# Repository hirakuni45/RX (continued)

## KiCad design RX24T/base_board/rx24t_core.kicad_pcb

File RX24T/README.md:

## RX24T features / 特徴

- RXv2 core / RXv2 コア
- Maximum operating frequency 80MHz / 最大動作周波数 80MHz
- Single-precision 32-bit floating point / 32 ビット単精度浮動小数点
- 2.7V ～ 5.5V Operation / 動作
- 12 Bits A/D / １２ビットＡ／Ｄ変換器
- 8 Bits D/A / ８ビットＤ／Ａ変換器

### Package/パッケージ

|R5F524T---XX|Package/パッケージ|Pin/ピン数|Pitch/ピッチ|
|---|:-:|:-:|:-:|
|R5F524TxxxFP|LFQFP|100|0.50|
|R5F524TxxxFF|LQFP|80|0.65|
|R5F524TxxxFN|LFQFP|80|0.50|
|R5F524TxxxFM|LFQFP|64|0.50|

### Ambient operating temperature/動作周囲温度

|R5F524T--X--|degree Celsius|
|---|:-:|
|R5F524TxxDxx|-40 ～ +85℃|

### Memoey size/メモリ容量

|R5F524TX----|CodeFlash|RAM|DataFlash|ChipVersion|
|---|:-:|:-:|:-:|:-:|
|R5F524TExxxx|512K|32K|8K|B|
|R5F524TCxxxx|384K|32K|8K|B|
|R5F524TBxxxx|256K|32K|8K|B|
|R5F524TAxxxx|256K|16K|8K|A|
|R5F524T8xxxx|128K|16K|8K|A|

### Data Flash/データ・フラッシュ

|Capacity|Erase Size|Blank Check Size|Write Size|Erase Value|ID|
|:-:|:-:|:-:|:-:|:-:|:-:|
|8K|1024|1/1024|1|0xFF|4|

---

## RX24T Linker file / リンカーファイル

|Type|Code Flash|RAM|Data Flash|Linker File|Ustack|Istack|
|---|:-:|:-:|:-:|---|:-:|:-:|
|R5F524TA|256K|16K|8K|[R5F524TA.ld](R5F524TA.ld?ts=4)|1024|512|
|R5F524T8|128K|16K|8K|[R5F524T8.ld](R5F524T8.ld?ts=4)|1024|512|

---

## RX24T Dedicated class / 専用クラス

|Function/機能|Source|Remarks/備考|
|---|---|:-:|
|Peripheral Name/ペリフェラル名|[peripheral.hpp](peripheral.hpp?ts=4)||
|Hardware-specific Definition/ハード固有定義|[board_profile.hpp](board_profile.hpp?ts=4)||
|Operating Frequency Definition/動作周波数定義|[clock_profile.hpp](clock_profile.hpp?ts=4)||
|Power Control/電力制御|[power_mgr.hpp](power_mgr.hpp?ts=4)||
|Port Definition/ポート定義|[port.hpp](port.hpp?ts=4)||
|Interrupt Definition/割り込み定義|[icu.hpp](icu.hpp?ts=4)||
|Interrupt Management/割り込み管理|[icu_mgr.hpp](icu_mgr.hpp?ts=4)||
|Port Function Definition/ポート機能定義|[mpc.hpp](mpc.hpp?ts=4)||
|Port Mapping/ポートマッピング|[port_map.hpp](port_map.hpp?ts=4)||
|Port Mapping IRQ/ポートマッピング IRQ|[port_map_irq.hpp](port_map_irq.hpp?ts=4)||
|Port Mapping MTU/ポートマッピング MTU|[port_map_mtu.hpp](port_map_mtu.hpp?ts=4)||
|Port Mapping TMR/ポートマッピング TMR|[port_map_tmr.hpp](port_map_tmr.hpp?ts=4)||
|Port Mapping GPT/ポートマッピング GPT|[port_map_gpt.hpp](port_map_gpt.hpp?ts=4)||
|FLASH Definition/FLASH 定義|[flash.hpp](flash.hpp?ts=4)||
|FLASH Definition/FLASH I/O 定義|[flash_io.hpp](flash_io.hpp?ts=4)||
|LVDA Definition/LVDA 定義|[lvda.hpp](lvda.hpp?ts=4)||
|POE3 Definition/POE3 定義|[poe2.hpp](poe3.hpp?ts=4)||
|D/A Definition/D/A 定義|[da.hpp](da.hpp?ts=4)||
|A/D Definition/A/D 定義|[s12ad.hpp](s12ad.hpp?ts=4)||
|System Definition/システム定義|[system.hpp](system.hpp?ts=4)||
|System I/O Definition/システム I/O 定義|[system_io.hpp](system_io.hpp?ts=4)||

---

## Basic Pin Assignments / 基本ピンアサイン

|Terminal/端子|LFQFP 100|
|---|---|
|VCL|VCL(5)|
|Reset Input/リセット入力|RES#(10)|
|Mode Controle/モード制御|MD/FINED(6)|
|RXD|PD5/RXD1(20)|
|TXD|PD3/TXD1(22)|
|Power/電源|VCC(14), VCC(29), VCC(42), VCC(60)|
|GND/接地|VSS(3), VSS(12), VSS(31), VSS(44), VSS(62)|
|Analog Power/アナログ電源|AVCC0(93), AVCC1(92), AVCC2(71)|
|Analog GND/アナログ接地|AVSS0(94), AVSS1(95), AVSS2(73)|
|Analog Refarence/アナログ基準電源|VREF(72)|
|OSC in|EXTAL(13)|
|OSC out|XTAL(11)|

- VCL: 4.7uF/25V

|Mode/モード|MD|
|---|:---:|
|Serial BOOT/シリアルブート|0|
|Single Chip/シングルチップ|1|

---

## Device, Renesas / デバイス、ルネサス

- [device.hpp (SIG_RX24T)](../common/device.hpp?ts=4)
- [renesas.hpp (SIG_RX24T)](../common/renesas.hpp?ts=4)

|name space|Device, Renesas|デバイス、ルネサス|
|---|---|---|
|[clock_profile](../RX24T/clock_profile?ts=4)|Clock Profile|クロック・プロファイル|
|[SYSTEM](../RX24T/system.hpp?ts=4)|Clock Generation Circuit|クロック発生回路|
|[power_mgr](../RX24T/power_mgr.hpp?ts=4)|Low Power Consumption|消費電力低減機能|
|[ICU](../RX24T/icu.hpp?ts=4)|Interrupt Controller|割り込みコントローラ|
|[icu_mgr](../RX24T/icu_mgr.hpp?ts=4)|ICU Manager|ICU マネージャー|
|[MPC](../RX24T/mpc.hpp?ts=4)|Multi-Function Pin Controller|マルチファンクションピンコントローラ|
|[PORTx](../RX24T/port.hpp?ts=4)|I/O Ports|I/O ポート|
|[port_map](../RX24T/port_map.hpp?ts=4)|Port Mapping|ポート・マッピング|
|[port_map_mtu](../RX24T/port_map_mtu.hpp?ts=4)|Port Mapping MTU|ポート・マッピング MTU|
|[port_map_tmr](../RX24T/port_map_tmr.hpp?ts=4)|Port Mapping TMR|ポート・マッピング TMR|
|[port_map_irq](../RX24T/port_map_irq.hpp?ts=4)|Port Mapping IRQ|ポート・マッピング IRQ|
|[FLASH](../RX24T/flash.hpp?ts=4)|Flash Memory|フラッシュメモリ|
|[SYSTEM_IO](../RX24T/system_io.hpp?ts=4)|System In/Out (Clock Setting)|システム In/Out (クロック設定)|
|[FLASH_IO](../RX24T/flash_io.hpp?ts=4)|Flash In/Out|フラッシュ In/Out|
|[adc_in](../RX24T/adc_in.hpp?ts=4)|A/D Converter Input|A/D 変換入力|
|[dac_out](../RX24T/dac_out.hpp?ts=4)|D/A Converter Output|D/A 変換出力|
|[board_profile](../RX24T/board_profile?ts=4)|Board Profile|ボード・プロファイル|

---

## Peripheral / ペリフェラル

- [peripheral.hpp](peripheral.hpp?ts=4)

|Peripheral|Function|機能|
|---|---|---|
|[CAC](../RX600/cac.hpp?ts=4)|Clock Frequency Accuracy Measurement Circuit|クロック周波数精度測定回路|
|[DTC](../RX600/dtc.hpp?ts=4)|Data Transfer Controller|データトランスファコントローラ|
|[MTU0](../RX600/mtu3.hpp?ts=4)|Multi-Function Timer Pulse Unit 0|マルチファンクションタイマパルスユニット０|
|[MTU1](../RX600/mtu3.hpp?ts=4)|Multi-Function Timer Pulse Unit 1|マルチファンクションタイマパルスユニット１|
|[MTU2](../RX600/mtu3.hpp?ts=4)|Multi-Function Timer Pulse Unit 2|マルチファンクションタイマパルスユニット２|
|[MTU3](../RX600/mtu3.hpp?ts=4)|Multi-Function Timer Pulse Unit 3|マルチファンクションタイマパルスユニット３|
|[MTU4](../RX600/mtu3.hpp?ts=4)|Multi-Function Timer Pulse Unit 4|マルチファンクションタイマパルスユニット４|
|[MTU5](../RX600/mtu3.hpp?ts=4)|Multi-Function Timer Pulse Unit 5|マルチファンクションタイマパルスユニット５|
|[MTU6](../RX600/mtu3.hpp?ts=4)|Multi-Function Timer Pulse Unit 6|マルチファンクションタイマパルスユニット６|
|[MTU7](../RX600/mtu3.hpp?ts=4)|Multi-Function Timer Pulse Unit 7|マルチファンクションタイマパルスユニット７|
|[MTU9](../RX600/mtu3.hpp?ts=4)|Multi-Function Timer Pulse Unit 9|マルチファンクションタイマパルスユニット９|
|[POE3](../RX600/poe3.hpp?ts=4)|Port Output Enable 3|ポートアウトプットイネーブル３|
|[GPT0](../RX600/gpt.hpp?ts=4)|General PWM Timer 0|汎用 PWM タイマ０|
|[GPT1](../RX600/gpt.hpp?ts=4)|General PWM Timer 1|汎用 PWM タイマ１|
|[GPT2](../RX600/gpt.hpp?ts=4)|General PWM Timer 2|汎用 PWM タイマ２|
|[GPT3](../RX600/gpt.hpp?ts=4)|General PWM Timer 3|汎用 PWM タイマ３|
|[TMR0](../RX600/tmr.hpp?ts=4)|8-Bit Timer 0|8 ビットタイマ０|
|[TMR1](../RX600/tmr.hpp?ts=4)|8-Bit Timer 1|8 ビットタイマ１|
|[TMR2](../RX600/tmr.hpp?ts=4)|8-Bit Timer 2|8 ビットタイマ２|
|[TMR3](../RX600/tmr.hpp?ts=4)|8-Bit Timer 3|8 ビットタイマ３|
|[TMR4](../RX600/tmr.hpp?ts=4)|8-Bit Timer 4|8 ビットタイマ４|
|[TMR5](../RX600/tmr.hpp?ts=4)|8-Bit Timer 5|8 ビットタイマ５|
|[TMR6](../RX600/tmr.hpp?ts=4)|8-Bit Timer 6|8 ビットタイマ６|
|[TMR7](../RX600/tmr.hpp?ts=4)|8-Bit Timer 7|8 ビットタイマ７|
|[CMT0](../RX600/cmpc.hpp?ts=4)|Compare Match Timer 0|コンペアマッチタイマ０|
|[CMT1](../RX600/cmpc.hpp?ts=4)|Compare Match Timer 1|コンペアマッチタイマ１|
|[CMT2](../RX600/cmpc.hpp?ts=4)|Compare Match Timer 2|コンペアマッチタイマ２|
|[CMT3](../RX600/cmpc.hpp?ts=4)|Compare Match Timer 3|コンペアマッチタイマ３|
|[IWDT](../RX600/iwdt.hpp?ts=4)|Independent Watchdog Timer|独立ウォッチドッグタイマ|
|[SCI1](../RX600/sci_g.hpp?ts=4)|Serial Communications Interface 1|シリアルコミュニケーションインタフェース１|
|[SCI5](../RX600/sci_g.hpp?ts=4)|Serial Communications Interface 5|シリアルコミュニケーションインタフェース５|
|[SCI6](../RX600/sci_g.hpp?ts=4)|Serial Communications Interface 6|シリアルコミュニケーションインタフェース６|
|[RIIC0](../RX600/riic.hpp?ts=4)|I2C-bus Interface 0|I2C バスインタフェース０|
|[RSCAN](../RX600/rscan.hpp?ts=4)|RSCAN Module|RSCAN モジュール|
|[RSPI0](../RX600/rspi.hpp?ts=4)|Serial Peripheral Interface 0|シリアルペリフェラルインタフェース０|
|[CRC](../RX600/crc.hpp?ts=4)|CRC Calculator|CRC 演算器|
|[S12AD](../RX24T/s12ad.hpp?ts=4)|12-Bit A/D Converter|12 ビット A/D コンバータ|
|[S12AD1](../RX24T/s12ad.hpp?ts=4)|12-Bit A/D Converter 1|12 ビット A/D コンバータ１|
|[S12AD2](../RX24T/s12ad.hpp?ts=4)|12-Bit A/D Converter 2|12 ビット A/D コンバータ２|
|[DA](../RX24T/da.hpp?ts=4)|8-Bit D/A Converter|8 ビット D/A コンバータ|
|[CMPC0](../RX600/cmpc.hpp?ts=4)|Comparator C0|コンパレーターＣ０|
|[CMPC1](../RX600/cmpc.hpp?ts=4)|Comparator C1|コンパレーターＣ１|
|[CMPC2](../RX600/cmpc.hpp?ts=4)|Comparator C2|コンパレーターＣ２|
|[CMPC3](../RX600/cmpc.hpp?ts=4)|Comparator C3|コンパレーターＣ３|
|[DOC](../RX600/doc.hpp?ts=4)|Data Operation Circuit|データ演算回路|

---

## Port map order (IRQ) / ポートマップ候補 (IRQ)

- [port_map_irq.hpp](port_map_irq.hpp?ts=4)

### LFQGFP100

|IRQ|FIRST|SECOND|THIRD|FOURTH|FIFTH|
|---|---|---|---|---|---|
|IRQ0|P10 (100)|P52 (81)|PE5 (1)|-|-|
|IRQ1|P11 (99)|P53 (80)|PA5 (36)|PE4 (8)|-|
|IRQ2|P00 (4)|P54 (79)|PD4 (21)|PE3 (9)|-|
|IRQ3|P55 (78)|PB4 (30)|PD5 (20)|-|-|
|IRQ4|P01 (7)|P60 (77)|P96 (43)|-|-|
|IRQ5|P02 (2)|P61 (76)|P70 (57)|PB6 (27)|PD6 (19)|
|IRQ6|P21 (67)|P31 (61)|P62 (75)|-|-|
|IRQ7|P20 (68)|P30 (63)|P63 (74)|-|-|

---

## Port map order / ポートマップ候補

- [port_map.hpp](port_map.hpp?ts=4)

### LFQFP100

|Peripheral|FIRST|SECOND|THIRD|
|---|---|---|---|
|SCI1 / RXD|PD5 (20)|-|-|
|SCI1 / TXD|PD3 (22)|-|-|
|SCI1 / SCK|PD4 (21)|-|-|
|SCI5 / RXD|PB6 (27)|PE0 (17)|-|
|SCI5 / TXD|PB5 (28)|PD7 (18)|-|
|SCI5 / SCK|PB7 (26)|PD2 (23)|-|
|SCI6 / RXD|P80 (98)|PA5 (36)|PB1 (34)|
|SCI6 / TXD|P81 (97)|PB0 (35)|PB2 (33)|
|SCI6 / SCK|P82 (96)|PA4 (37)|PB3 (32)|
|RIIC0 / SCL|PB1 (34)|-|-|
|RIIC0 / SDA|PB2 (33)|-|-|
|RSCAN / CRX|PA0 (41)|-|-|
|RSCAN / CTX|PA1 (40)|-|-|
|RSPI0 / RSPCK|P24 (64)|PB3 (32)|PD0 (25)|
|RSPI0 / MOSI|P23 (65)|PB0 (35)|PD2 (23)|
|RSPI0 / MISO|P22 (66)|PA5 (36)|PD1 (24)|
|RSPI0 / SSL0|P30 (63)|PA3 (38)|PD6 (19)|
|RSPI0 / SSL1|P31 (61)|PA2 (39)|PD7 (18)|
|RSPI0 / SSL2|P32 (59)|PA1 (40)|PE0 (17)|
|RSPI0 / SSL3|P33 (58)|PA0 (41)|PE1 (16)|

---

## Port map order (GPT) / ポートマップ候補 (GPT)

- [port_map_gpt.hpp](port_map_gpt.hpp?ts=4)

### LFQFP100

|GPT|FIRST|SECOND|THIRD|
|---|---|---|---|
|GTIOC0A|P71 (56)|PD7 (18)|-|
|GTIOC0B|P74 (53)|PD1 (24)|-|
|GTIOC1A|P72 (55)|PD0 (25)|-|
|GTIOC1B|P75 (52)|PB7 (26)|-|
|GTIOC2A|P73 (54)|PB6 (27)|-|
|GTIOC2B|P76 (51)|PB5 (28)|-|
|GTIOC3A|PD7 (18)|-|-|
|GTIOC3B|PD6 (19)|-|-|
|GTECLKA|PD5 (20)|-|-|
|GTECLKB|PD4 (21)|-|-|
|GTECLKC|PD3 (22)|-|-|
|GTECLKD|PB4 (30)|-|-|
|GTETRG|PB4 (30)|-|-|
|GTADSM0|PA3 (38)|-|-|
|GTADSM1|PA2 (39)|-|-|

---

## Port map order (MTU) / ポートマップ候補 (MTU)

[port_map_mtu.hpp](port_map_mtu.hpp?ts=4)

### LFQGFP100

|MTU|FIRST|SECOND|THIRD|
|---|---|---|---|
|MTIOC0A #|P31 (61)|PB3 (32)|-|
|MTIOC0B #|P30 (63)|PB2 (33)|-|
|MTIOC0C #|PB1 (34)|-|-|
|MTIOC0D #|PB0 (35)|-|-|
|MTIOC1A #|PA5 (36)|-|-|
|MTIOC1B #|PA4 (37)|-|-|
|MTIOC2A #|PA3 (38)|-|-|
|MTIOC2B #|PA2 (39)|-|-|
|MTIOC3A #|P11 (99)|P33 (58)|-|
|MTIOC3B #|P71 (56)|-|-|
|MTIOC3C #|P32 (59)|-|-|
|MTIOC3D #|P74 (53)|-|-|
|MTIOC4A #|P72 (55)|-|-|
|MTIOC4B #|P73 (54)|-|-|
|MTIOC4C #|P75 (52)|-|-|
|MTIOC4D #|P76 (51)|-|-|
|MTIC5U #|P24 (64)|P82 (96)|-|
|MTIC5V #|P23 (65)|P81 (97)|-|
|MTIC5W #|P22 (66)|P80 (98)|-|
|MTIOC6A #|PA1 (40)|-|-|
|MTIOC6B #|P95 (45)|-|-|
|MTIOC6C #|PA0 (41)|-|-|
|MTIOC6D #|P92 (48)|-|-|
|MTIOC7A #|P94 (46)|-|-|
|MTIOC7B #|P93 (47)|-|-|
|MTIOC7C #|P91 (49)|-|-|
|MTIOC7D #|P90 (50)|-|-|
|MTIOC9A #|P21 (67)|PD7 (18)|-|
|MTIOC9B #|P10 (100)|PE0 (17)|-|
|MTIOC9C #|P20 (68)|PD6 (19)|-|
|MTIOC9D #|P02 (2)|PE1 (16)|-|
|MTCLKA #|P21 (67)|P33 (58)|-|
|MTCLKB #|P20 (68)|P32 (59)|-|
|MTCLKC #|P11 (99)|P31 (61)|PE4 (8)|
|MTCLKD #|P10 (100)|P30 (63)|PE3 (9)|
|ADSM0|PB2 (33)|-|-|
|ADSM1|PB1 (34)|-|-|

---

## Port map order (TMR) / ポートマップ候補 (TMR)

- [port_map_tmr.hpp](port_map_tmr.hpp?ts=4)

### LFQFP100

|TMR|FIRST|SECOND|THIRD|FOURTH|
|---|---|---|---|---|
|TMO0|PD3 (22)|P33 (58)|PB0 (35)|-|
|TMCI0|PD4 (21)|PB1 (34)|-|-|
|TMRI0|PD5 (20)|PB2 (33)|-|-|
|TMO1|PD6 (19)|-|-|-|
|TMCI1|PD2 (23)|PE0 (17)|-|-|
|TMRI1|PD7 (18)|-|-|-|
|TMO2|P23 (65)|PA0 (41)|PD1 (24)|-|
|TMCI2|P24 (64)|-|-|-|
|TMRI2|P22 (66)|-|-|-|
|TMO3|P11 (99)|-|-|-|
|TMCI3|PA5 (36)|-|-|-|
|TMRI3|P10 (100)|-|-|-|
|TMO4|P22 (66)|P82 (96)|PA1 (40)|PD2 (23)|
|TMCI4|P21 (67)|P81 (97)|-|-|
|TMRI4|P20 (68)|P80 (98)|-|-|
|TMO5|PE1 (16)|-|-|-|
|TMCI5|PE0 (17)|-|-|-|
|TMRI5|PD7 (18)|-|-|-|
|TMO6|P24 (64)|P32 (59)|PD0 (25)|-|
|TMCI6|P30 (63)|PD4 (21)|-|-|
|TMRI6|P31 (61)|PD5 (20)|-|-|
|TMO7|PA2 (39)|-|-|-|
|TMCI7|PA4 (37)|-|-|-|
|TMRI7|PA3 (38)|-|-|-|

---

## 12 Bits A/D Converter input (S12AD) / 12 ビット A/D コンバーター入力 (S12AD)

- [s12ad.hpp](s12ad.hpp?ts=4)

### LFQFP100

|S12AD/ANALOG|Port|
|---|---|
|AN000|P40 (91)|
|AN001|P41 (90)|
|AN002|P42 (89)|
|AN003|P43 (88)|
|AN016|P20 (68)|

|S12AD1/ANALOG|Port|
|---|---|
|AN100|P44 (87)|
|AN101|P45 (86)|
|AN102|P46 (85)|
|AN103|P47 (84)|
|AN116|P21 (67)|

|S12AD2/ANALOG|Port|
|---|---|
|AN200|P60 (77)|
|AN201|P61 (76)|
|AN202|P62 (75)|
|AN203|P63 (74)|
|AN204|P64 (70)|
|AN205|P65 (69)|
|AN206|P50 (83)|
|AN207|P51 (82)|
|AN208|P52 (81)|
|AN209|P53 (80)|
|AN210|P54 (79)|
|AN211|P55 (78)|

---

## 8 Bits D/A Converter output (DA) / 8 ビット D/A コンバーター出力 (DA)

- [da.hpp](da.hpp?ts=4)

### LFQFP100

|DA/ANALOG|Port|
|---|---|
|DA0|P24 (64)|
|DA1|P23 (65)|

---

## rx_prog Flash Programming / rx_prog フラッシュプログラム

||Support/サポート|operation verification/動作検証|
|-|:-:|:-:|
|[rxprog](../rxprog)|〇|〇|

---

Translated with www.DeepL.com/Translator (free version)

---

## License

[MIT](../LICENSE)

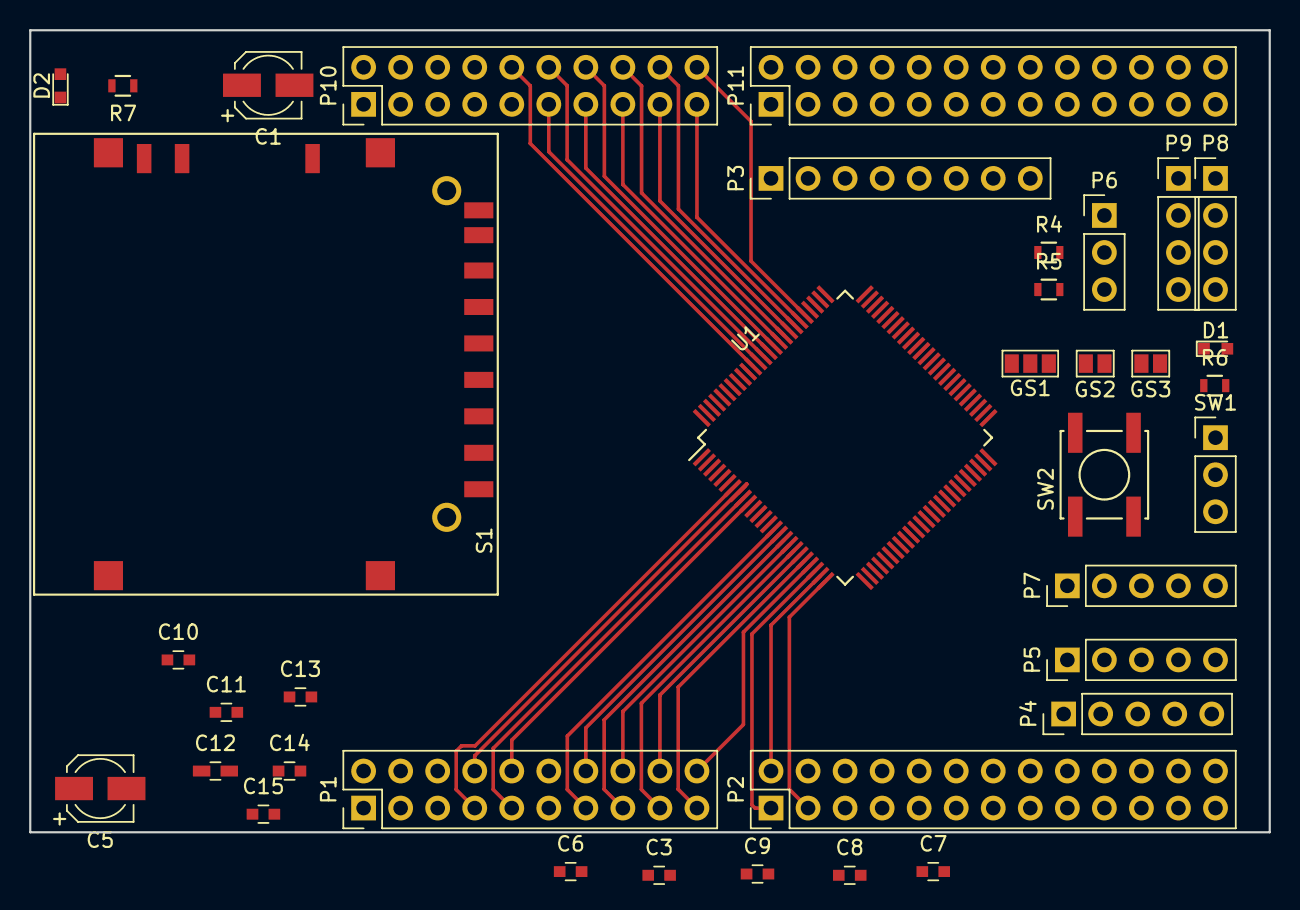
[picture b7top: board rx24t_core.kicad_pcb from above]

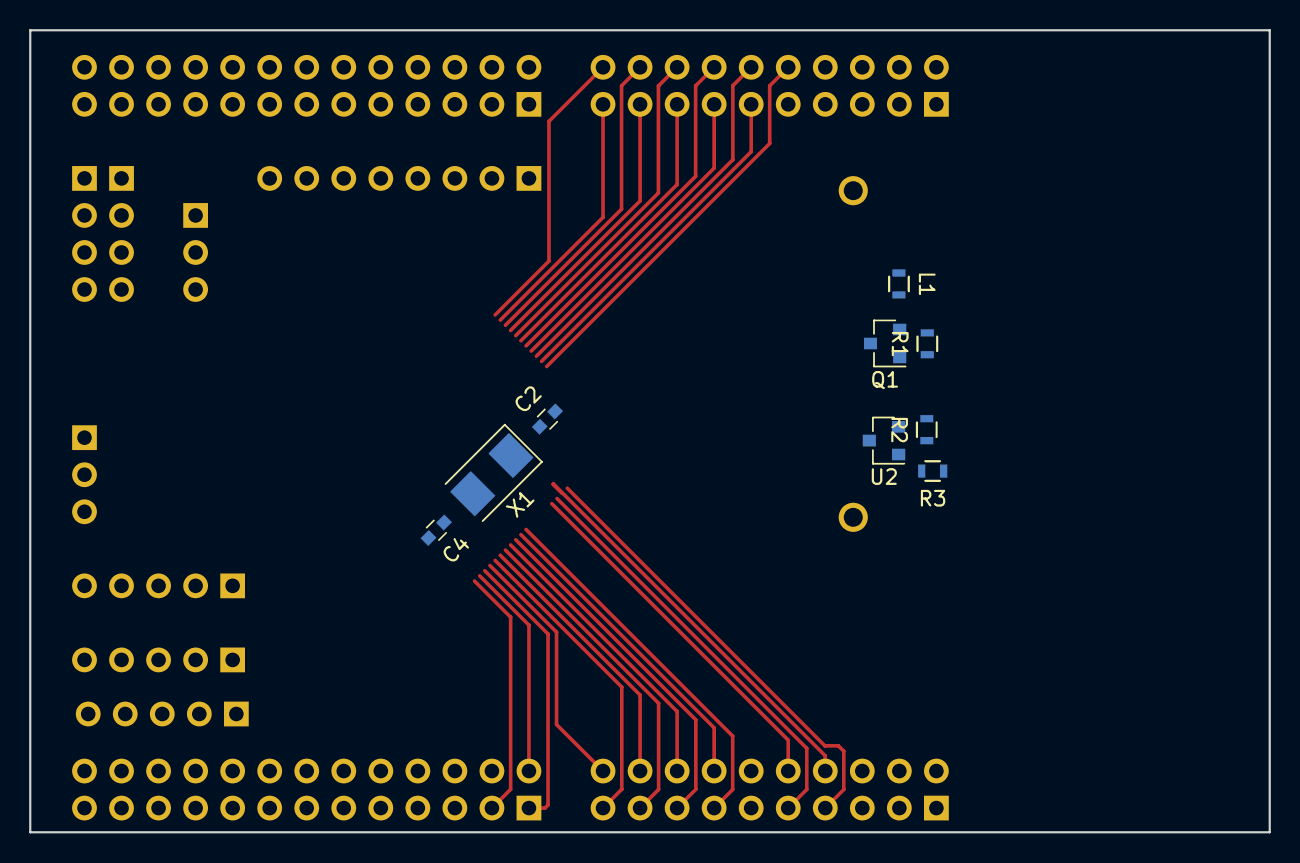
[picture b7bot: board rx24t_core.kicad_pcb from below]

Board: 2 copper layers, 85.0 x 55.0 mm, 46 parts (9 on the bottom side), 94 nets.

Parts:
C1: 22uF; CP_Elec_4x5.8
C2, C4: 10pF; C_0603
C3: 4.7uF; C_0603
C5: 47uF; CP_Elec_4x5.8
C6, C7, C8, C9, C10, C11, C13, C14, C15: 0.1uF; C_0603
C12: 1uF; C_0603_HandSoldering
D1, D2: LED; LED_0603
GS1: GS3
GS2, GS3: GS2
L1: FB; R_0603
P1, P10: 2X10; Pin_Header_Straight_2x10_Pitch2.54mm
P2, P11: 2X13; Pin_Header_Straight_2x13_Pitch2.54mm
P3: SPI-LCD; Pin_Header_Straight_1x08_Pitch2.54mm
P4: SCI1; Pin_Header_Straight_1x05_Pitch2.54mm
P5: SCI5; Pin_Header_Straight_1x05_Pitch2.54mm
P6: APOWER; Pin_Header_Straight_1x03_Pitch2.54mm
P7: SCI6; Pin_Header_Straight_1x05_Pitch2.54mm
P8, P9: I2C; Pin_Header_Straight_1x04_Pitch2.54mm
Q1: DMG3415U; SOT-23(DMG3415U)
R1: 47K; R_0603
R2, R3: 10K; R_0603
R4, R5, R6, R7: 1K; R_0603
S1: SD-CARD; DM1AA-SF-PEJ
SW1: 3P-SW; Pin_Header_Straight_1x03_Pitch2.54mm
SW2: RESET; SW_SPST_EVPBF
U1: RX24T; LQFP-100_14x14mm_Pitch0.5mm
U2: TCM809R; SOT-23
X1: 10MHz; Crystal_SMD_5032-2pin_5.0x3.2mm

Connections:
+3.3VADC: C11.1, C13.1, C14.1, GS3.1, P6.1, P10.5, U1.71, U1.92, U1.93
+3V3: C5.2, C6.1, C7.1, C8.1, C9.1, C10.1, C15.1, GS3.2, L1.2, P1.5, P1.12, P2.8, P3.1, P3.7, P4.4, P5.4, P7.4, P8.2, P9.2, P11.8, R2.1, R3.1, R4.1, R5.1, R6.1, U1.14, U1.29, U1.42, U1.60, U2.3
//RES: P1.10, P3.3, R2.2, SW2.1, U1.10, U2.2
/MD: P1.6, R3.2, SW1.2, U1.6
/P00: D1.1, P1.4, U1.4
/P01: P1.7, U1.7
/P02: P1.2, U1.2
/P10: P10.2, U1.100
/P11: P10.1, U1.99
/P20: P11.11, U1.68
/P21: P11.12, U1.67
/P22: P11.13, S1.7, U1.66
/P23: P3.6, P11.14, S1.2, U1.65
/P24: P3.5, P11.15, S1.5, U1.64
/P30: P11.16, U1.63
/P31: P11.17, U1.61
/P32: P11.18, U1.59
/P33: P11.19, U1.58
/P40: P10.9, U1.91
/P41: P10.10, U1.90
/P42: P10.11, U1.89
/P43: P10.12, U1.88
/P44: P10.13, U1.87
/P45: P10.14, U1.86
/P46: P10.15, U1.85
/P47: P10.16, U1.84
/P50: P10.17, U1.83
/P51: P10.18, U1.82
/P52: P10.19, U1.81
/P53: P10.20, U1.80
/P54: P11.1, U1.79
/P55: P11.2, U1.78
/P60: P11.3, S1.12, U1.77
/P61: P3.2, P11.4, U1.76
/P62: P3.4, P11.5, U1.75
/P63: P11.6, S1.10, U1.74
/P64: GS1.1, P11.9, U1.70
/P65: P11.10, S1.1, U1.69
/P70: P11.20, U1.57
/P71: P11.21, U1.56
/P72: P11.22, U1.55
/P73: P11.23, U1.54
/P74: P11.24, U1.53
/P75: P11.25, U1.52
/P76: P11.26, U1.51
/P80: P10.4, U1.98
/P81: P10.3, U1.97
/P82: P10.6, U1.96
/P90: P2.26, U1.50
/P91: P2.25, U1.49
/P92: P2.24, U1.48
/P93: P2.23, U1.47
/P94: P2.22, U1.46
/P95: P2.21, U1.45
/P96: P2.20, U1.43
/PA0: P2.19, U1.41
/PA1: P2.18, U1.40
/PA2: P2.17, U1.39
/PA3: P2.16, U1.38
/PA4: P2.15, P7.5, U1.37
/PA5: P2.14, P7.2, U1.36
/PB0: P2.13, P7.3, U1.35
/PB1: P2.12, P8.4, P9.4, R5.2, U1.34
/PB2: P2.11, P8.3, P9.3, R4.2, U1.33
/PB3: P2.10, U1.32
/PB4: P2.9, U1.30
/PB5: P2.6, P5.3, U1.28
/PB6: P2.5, P5.2, U1.27
/PB7: P2.4, P5.5, U1.26
/PD0: P2.3, U1.25
/PD1: P2.2, U1.24
/PD2: P2.1, U1.23
/PD3: P1.20, P4.3, U1.22
/PD4: P1.19, P4.5, U1.21
/PD5: P1.18, P4.2, U1.20
/PD6: P1.17, U1.19
/PD7: P1.16, U1.18
/PE0: P1.15, U1.17
/PE1: P1.14, U1.16
/PE2: P1.13, U1.15
/PE3: P1.9, U1.9
/PE4: P1.8, U1.8
/PE5: P1.1, U1.1
GND: C1.1, C2.2, C3.2, C4.2, C5.1, C6.2, C7.2, C8.2, C9.2, C10.2, C15.2, GS1.3, GS2.2, P1.3, P1.11, P2.7, P3.8, P4.1, P5.1, P7.1, P8.1, P9.1, P10.8, P11.7, R7.2, S1.3, S1.6, S1.11, SW1.3, SW2.2, U1.3, U1.12, U1.31, U1.44, U1.62, U2.1
GNDA: C11.2, C12.2, C13.2, C14.2, GS2.1, P6.3, P10.7, U1.73, U1.94, U1.95
unnamed: C1.2, D2.2, Q1.D, S1.4
unnamed: C2.1, U1.11, X1.1
unnamed: C3.1, U1.5
unnamed: C4.1, U1.13, X1.2
unnamed: C12.1, P6.2, U1.72
unnamed: D1.2, R6.2
unnamed: D2.1, R7.1
unnamed: GS1.2, Q1.G, R1.1
unnamed: L1.1, Q1.S, R1.2

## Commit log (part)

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2024-04-15 Update: cleanup
2024-04-18 Update: add CMTW input/output port mapping
2024-04-22 Add: a new file
2024-04-22 Update: Edit include path for 'port_map_tmr.hpp'
2024-04-22 Update: Add TMR port enum
2024-04-24 Add: a new file (RX23T)
2024-04-24 Update: Support MCU for RX23T
2024-04-24 Update: Edit path for RX23T
2024-04-29 Add: a new file (for RX23T)
2024-05-11 Update: add new parts
2024-05-12 Add: a new project
2024-05-12 Add: a new parts for KiCAD
2024-07-15 Add: a new file (RX660)
2024-07-15 Update: add RX660 peripheral
2024-07-18 Update: cleanup SCI class
2024-07-18 Update: Change current compiler to 202405
2024-07-21 Update: Add default CAN port
2024-07-21 Update: Support CANFDCLK profile, controle for system clock divider
2024-07-26 Add: a new file (RXxxx/README.md)
2024-07-26 Update: cleanup (RXxxx/README.md)
2024-07-26 Update: Edit stack size
2024-07-27 Add: linker file (Flash: 128K)
2024-07-27 Fix: zero suppress for strings
2024-08-23 Update: fix first point number decode
2024-08-26 Update: add new color
2024-08-26 Update: binary, hexadecimal output
2024-08-27 Add: CALC_sample gui images
2024-08-27 Add: exec binary
2024-09-21 Update: Edit link (tab space)
2024-09-21 Update: fill_triangl
2024-09-21 Update: add spinboxt management
2024-09-21 Update: Add unit function
2024-09-24 Update: Resolution of time measurement changed to 250 KHz
2024-09-27 Update: flash program options
2024-09-27 Add: a new controller
2024-09-30 Update: SCI error handling
2024-10-07 Update: erase_page API
2024-10-25 Add: Support RX23W
2024-10-25 Update: Support RX260/RX261/RX23W
2024-10-26 Update: Support RX260/RX261
2024-10-26 Update: add youtube link
2024-10-26 Remove: a file
2024-11-02 Update: support quick erase page
2024-11-08 Update: Manage ethernet port map
2024-11-10 Update: Management ether port mapping
2024-11-10 Add: Support RX130
2024-11-10 Update: Support RX130
2024-11-12 Add: Support RX111
2024-11-12 Update: Support RX111
2024-11-18 Add: add RX113 Support file
2024-11-18 Add: Support RX113 project
2024-11-18 Update: Support RX113
2024-11-19 Update: rtc_io template
2024-11-23 Add: Support RX110
2024-11-23 Remove: delete a file
2024-11-23 Update: data flash r/w management
2024-11-24 Update: data flash management
2024-11-24 Update: Support RX26T
2024-11-26 Update: cleanup, management
2024-11-27 Fix: erase check area
2024-12-02 Add: ADC_sdample for RX140
2024-12-02 Update: adc_in management
2024-12-02 Update: change stack size
2024-12-03 Update: Erase-bank/Blank-bank size management
2024-12-05 Update: chage LED default port
2024-12-10 Update: Add a new file
2024-12-21 Update: 64 bit accesss
2025-01-29 Add: a new file (for RX23W)
2025-01-29 Update: Support RX23W
2025-02-12 Add: Support RX210
2025-02-13 Update: Support RX210
2025-02-26 Fix: RX23W rx_prog state
2025-04-02 Update: ldscript for gcc-8.3.0/rx.ld
2025-04-09 Update: fix LD script
2025-04-10 Update: compile options for RX220
2025-04-10 Update: Support RX220 port mapping
2025-04-10 Update: memory clear area setting
2025-05-15 Add: KiCAD My footprint
2025-06-01 Add: Add 128K/48K device linker file
2025-06-12 Update: manage aac codec
2025-06-12 Add: sound codec library
2025-08-26 Update: port map order list
2025-08-27 Update: port map order, cleanup
2025-08-28 Update: port map order (RSPI_SSL), cleanup
2025-08-31 Update: port map order list, cleanup
2025-09-03 Update: map order list, cleanup
2025-09-18 Update: peripheral, cleanup
2025-09-20 Update: peripheral list, cleanup
2025-09-20 Fix: EDMAC register typedef
2025-09-21 Update: RX24U/SCI port mapping
2025-09-22 Add: a new file at RX24U
2025-09-22 Update: move RX24U files
2025-09-22 Update: peripheral list
2025-09-22 Update: RX24U include path
2025-09-23 Update: change channel name (CLK_A to CLKA)
2025-09-23 Update: change GPT(W) trigger name
2025-09-25 Update: GPT/GPTW port map list, port map order
2025-09-26 Update: MTU port map, port map order list
2025-09-29 Update: MTU port map list, cleanup
2025-09-29 Fix: MTU port map management (RX62x)
2025-09-30 Update: MTU port order list, cleanup
2025-10-01 Update: MTU port map order list, cleanup
2025-10-02 Update: sound key A, 440Hz to 432Hz
2025-10-04 Update: write in IRQ pin number, cleanup
2025-10-05 Update: MTU/TRWER register management
2025-10-05 Update: write in port number for TMR port map class
2025-10-08 Update: IRQ port map order list, cleanup
2025-10-10 Update: write in port number
2025-10-11 Update: port map order list (TPU), cleanup
2025-10-12 Update: port map order list (TMR), cleanup
2025-10-12 Update: port map order list (QSPI), cleanup
2025-10-16 Update: port map order: USER
2025-11-20 Update: Name change peripheral for eternet controller
2025-11-20 Update: cleanup ethernet port order list
2025-11-22 Update: GPTW register class for RX26x, RX26T
2025-11-22 Update: cleanup port map order list (Ethernet)
2025-11-23 Update: cleanup GPTW
2025-11-23 Update: cleanup USB, USB port-map order list
2025-11-24 Update: cleanup USB port-map, order list
2025-11-25 Update: cleanup USB port-map order list
2025-11-27 Update: cleanup port-map order list
2025-11-27 Fix: USB port name
2025-11-27 Update: clock controle register
2025-11-27 Update: power management
2025-11-27 Fix: bold text
2025-11-27 Update: ECCRAM, STBRAM define
2025-12-04 Update: cleanup A/D port number
2025-12-04 Update: cleanup 48 pin packeage
2025-12-07 Update: cleanup A/D port list
2025-12-09 Update: cleanup D/A port pin list
2025-12-10 Update: cleanup D/A class
2025-12-13 Update: for under construction
2025-12-13 Update: link library options
2025-12-15 Update: Fix zero compare, inter level cast
2026-01-27 Add: a new project (RX140: KiCAD)
2026-01-27 Add: a new file (KiCAD)
2026-01-30 Update: Add peripheral, device, renesas link
2026-02-01 Update: Add renesas, device link
2026-03-09 Fix: A/D group conversion
2026-03-09 Update: SCI NSFE bit management
2026-03-09 Update: include path
2026-04-03 Add: a new file (RX21A)
2026-04-03 Update: path for RX21A
2026-04-04 Add: RX21A's device file
2026-04-04 Update: RX21A path
2026-04-06 Add: RX21A device files
2026-04-06 Update: Add path RX21A
2026-04-09 Update: compile option for C++20, unused boost
2026-04-15 Fix: motsx_io save func
2026-04-15 Update: read command management
2026-04-18 Update: ID management
2026-04-18 Add: id table source
2026-04-18 Update: Add id table section
2026-04-26 Add: RX14T project
2026-04-26 Update: add RX14T code
2026-04-28 Update: clock management
2026-04-28 Update: RX14T support
2026-04-28 Update: OFS/ID management
2026-05-01 Add: Support RX14T
2026-05-01 Update: Support RX14T
2026-05-08 Update: cleanup support RX14T
2026-05-10 Update: cleanup RX14T
2026-06-20 Update: sch/pcb
2026-06-20 Add: pin assign label
